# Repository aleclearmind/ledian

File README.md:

# ledian

Welcome to ledian, a color-coded terminal made out of LEDs.

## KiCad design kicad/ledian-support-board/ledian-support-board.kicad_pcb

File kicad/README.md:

# ledian: KiCad projects

This directory contains KiCad projects for PCBs that Ledian uses.
Projects were created with KiCad 7 with no dependencies from external libraries.

## ledian-2.0-small

Prototype of Ledian 2.0, small panel with just 40 LEDs used to create a proof of concept.

## ledian-support-board

Support board for the microcontroller ESP32-C6. The boards mounts the developing board for ESP32-C6 made by Waveshare.
The board has also
 - 3 ADCs to read all the analog signals from temperature/current sensors of PCBs and power supplies
 - a digital temperature/humidity/pressure sensor
 - power good input signals from power supplies
 - voltage level shifter 3.3V -> 5V for LEDs data signals

## ledian-2.0

Full version of Ledian, panels composed by 480 LEDs arranged in a 12 rows and 40 columns that can be tiled to create a standard 80x24 terminal.
Some changes were made to the configuration of signal input and 4 NTC were added to measure PCB's board temperature.

## ledian-LED-PCB-placer

KiCad's plugin that does the majority of the PCB routing for Ledian board with all the LEDs. The plugin procedurally created the
PCB, places all the componentes, routes all the traces and creates filled zones for ground and power supply.
The configurability is limited and very specific to Ledian but it already allows to change number of LEDs, spacing, position/width of traces and other parameters.

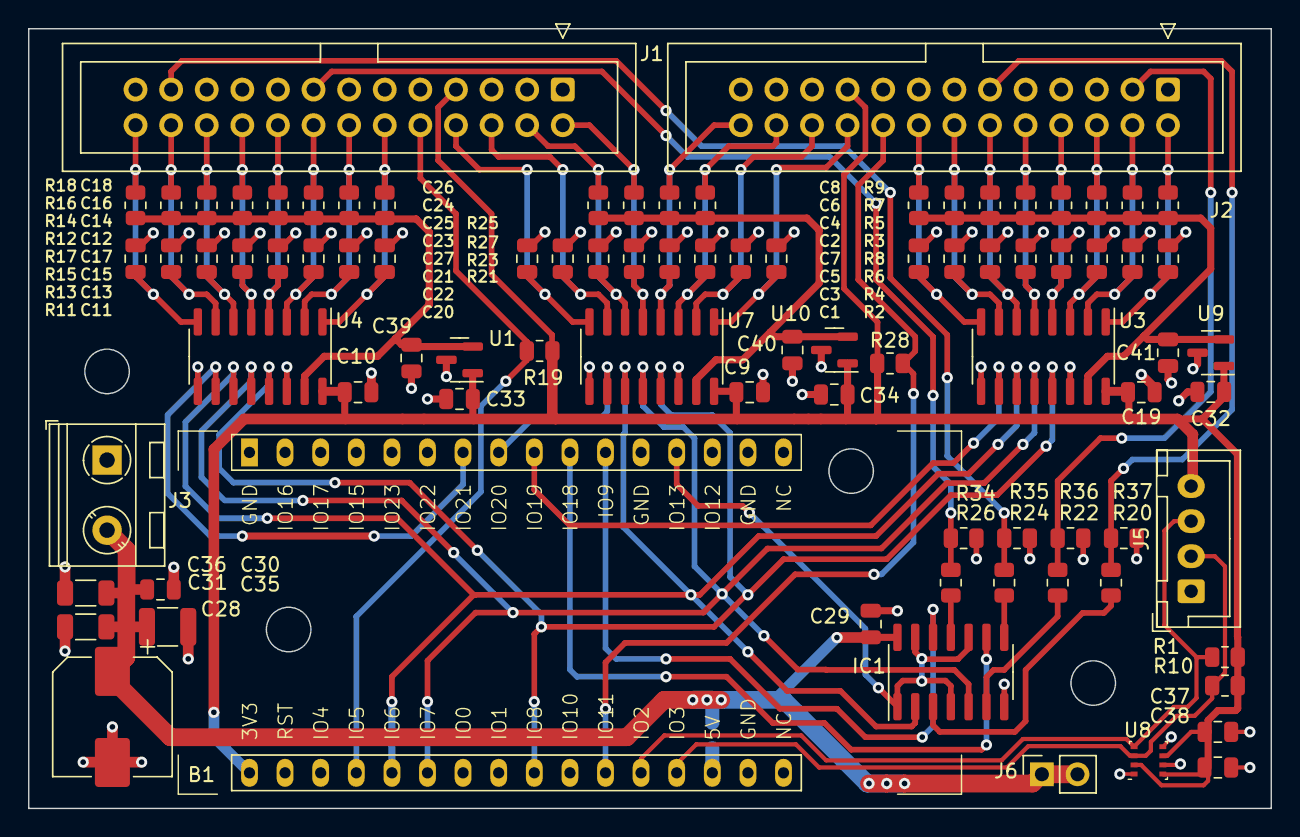
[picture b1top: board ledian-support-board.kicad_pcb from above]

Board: 2 copper layers, 88.6 x 55.6 mm, 88 parts (1 on the bottom side), 50 nets.

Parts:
B1: ESP32-C6_WaveShare
C1, C2, C3, C4, C5, C6, C7, C8, C11, C12, C13, C14, C15, C16, C17, C18, C21, C23, C25, C27: 2.2uF; C_0805_2012Metric
C9, C10, C19, C20, C22, C24, C26, C29, C30, C37, C38: 100nF; C_0805_2012Metric
C28: 100uF; CP_Elec_8x10
C31: 4.7uF; C_1206_3216Metric
C32, C33, C34: 0.47uF; C_0805_2012Metric
C35: 10uF; C_1210_3225Metric
C36: 1uF; C_1206_3216Metric
C39, C40, C41: 1uF; C_0805_2012Metric
IC1: SN74HCT125N; SOIC-14_3.9x8.7mm_P1.27mm
J1, J2: Conn_02x13_Odd_Even; IDC-Header_2x13_P2.54mm_Vertical
J3: TerminalBlock_RND_205-00045_1x02_P5.00mm_Horizontal
J5: Conn_01x04_Pin; JST_XH_B4B-XH-A_1x04_P2.50mm_Vertical
J6: Conn_01x02; PinSocket_1x02_P2.54mm_Vertical
R1, R10: 3.3k; R_0805_2012Metric
R2, R3, R4, R5, R6, R7, R8, R9, R11, R12, R13, R14, R15, R16, R17, R18, R21, R25: 1.6k; R_0805_2012Metric
R19, R28: 22k; R_0805_2012Metric
R20, R22, R24, R26: 300; R_0805_2012Metric
R23, R27: 750; R_0805_2012Metric
R29: 0; R_0805_2012Metric
R34, R35, R36, R37: 4.7k; R_0805_2012Metric
U1, U9, U10: REF3030; SOT-23
U3, U4, U7: MCP3208; SOIC-16_3.9x9.9mm_P1.27mm
U8: BME280; Bosch_LGA-8_2.5x2.5mm_P0.65mm_ClockwisePinNumbering

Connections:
+3V0: C39.1, C40.1, C41.1, R2.1, R3.1, R4.1, R5.1, R6.1, R7.1, R8.1, R9.1, R11.1, R12.1, R13.1, R14.1, R15.1, R16.1, R17.1, R18.1, R21.1, R23.1, R25.1, R27.1, U1.2 (OUT), U3.15 (Vref), U4.15 (Vref), U7.15 (Vref), U9.2 (OUT), U10.2 (OUT)
+3V3: B1.32 (3V3), C9.1, C10.1, C19.1, C32.1, C33.1, C34.1, C37.1, C38.1, J1.7, J2.19, J5.4, R1.1, R10.1, R19.1, R28.1, U1.1 (IN), U3.16 (Vdd), U4.16 (Vdd), U7.16 (Vdd), U8.2 (CSB), U8.6 (VDDIO), U8.8 (VDD), U9.1 (IN), U10.1 (IN)
+5V: C28.1, C29.1, C30.1, C31.1, C35.1, C36.1, IC1.14 (VCC), J3.2, J6.1, J6.2, R29.1
CUR_PANEL_0: C20.1, J2.20, U7.1 (CH0)
CUR_PANEL_1: C22.1, J2.22, U7.2 (CH1)
CUR_PANEL_2: C24.1, J1.6, U7.7 (CH6)
CUR_PANEL_3: C26.1, J1.8, U7.8 (CH7)
GND: B1.1 (GND), B1.12 (GND), B1.15 (GND), B1.18 (GND), C1.2, C2.2, C3.2, C4.2, C5.2, C6.2, C7.2, C8.2, C9.2, C10.2, C11.2, C12.2, C13.2, C14.2, C15.2, C16.2, C17.2, C18.2, C19.2, C20.2, C21.2, C22.2, C23.2, C24.2, C25.2, C26.2, C27.2, C28.2, C29.2, C30.2, C31.2, C32.2, C33.2, C34.2, C35.2, C36.2, C37.2, C38.2, C39.2, C40.2, C41.2, IC1.7 (GND), J1.1, J1.3, J1.5, J1.9, J1.11, J1.13, J1.17, J1.19, J1.21, J1.25, J2.1, J2.5, J2.7, J2.9, J2.13, J2.15, J2.17, J2.21, J2.23, J2.25, J3.1, J5.1, R34.1, R35.1, R36.1, R37.1, U1.3 (GND), U3.9 (DGND), U3.14 (AGND), U4.9 (DGND), U4.14 (AGND), U7.9 (DGND), U7.14 (AGND), U8.1 (GND), U8.5 (SDO), U8.7 (GND), U9.3 (GND), U10.3 (GND)
I2C_SCK: B1.21 (IO2), J5.3, R1.2, U8.4 (SCK)
I2C_SDA: B1.20 (IO3), J5.2, R10.2, U8.3 (SDI)
NTC_0_PANEL_0: C1.1, J2.2, R2.2, U3.1 (CH0)
NTC_0_PANEL_1: C2.1, J2.10, R3.2, U3.5 (CH4)
NTC_0_PANEL_2: C11.1, J1.12, R11.2, U4.1 (CH0)
NTC_0_PANEL_3: C12.1, J1.20, R12.2, U4.5 (CH4)
NTC_1_PANEL_0: C3.1, J2.4, R4.2, U3.2 (CH1)
NTC_1_PANEL_1: C4.1, J2.12, R5.2, U3.6 (CH5)
NTC_1_PANEL_2: C13.1, J1.14, R13.2, U4.2 (CH1)
NTC_1_PANEL_3: C14.1, J1.22, R14.2, U4.6 (CH5)
NTC_2_PANEL_0: C5.1, J2.6, R6.2, U3.3 (CH2)
NTC_2_PANEL_1: C6.1, J2.14, R7.2, U3.7 (CH6)
NTC_2_PANEL_2: C15.1, J1.16, R15.2, U4.3 (CH2)
NTC_2_PANEL_3: C16.1, J1.24, R16.2, U4.7 (CH6)
NTC_3_PANEL_0: C7.1, J2.8, R8.2, U3.4 (CH3)
NTC_3_PANEL_1: C8.1, J2.16, R9.2, U3.8 (CH7)
NTC_3_PANEL_2: C17.1, J1.18, R17.2, U4.4 (CH3)
NTC_3_PANEL_3: C18.1, J1.26, R18.2, U4.8 (CH7)
NTC_PSU_0: C21.1, J2.24, R21.2, U7.3 (CH2)
NTC_PSU_1: C25.1, J1.4, R25.2, U7.6 (CH5)
unnamed: B1.19 (5V), R29.2
unnamed: IC1.3 (1Y), R20.1
unnamed: IC1.6 (2Y), R22.1
unnamed: IC1.8 (3Y), R24.1
unnamed: IC1.11 (4Y), R26.1
PHOTORESIST_0: C23.1, J2.26, R23.2, U7.4 (CH3)
PHOTORESIST_1: C27.1, J1.2, R27.2, U7.5 (CH4)
PSU_GOOD_0: B1.22 (IO11), J2.18, R28.2
PSU_GOOD_1: B1.29 (IO5), J1.10, R19.2
SPI_CLK: B1.24 (IO8), U3.13 (CLK), U4.13 (CLK), U7.13 (CLK)
SPI_CS_ADC_0: B1.9 (IO19), U3.10 (~CS/SHDN)
SPI_CS_ADC_1: B1.7 (IO21), U4.10 (~CS/SHDN)
SPI_CS_ADC_2: B1.8 (IO20), U7.10 (~CS/SHDN)
SPI_CS_LED: B1.13 (IO13), IC1.1 (1~OE), IC1.4 (2~OE), IC1.10 (3~OE), IC1.13 (4~OE)
SPI_IO_0: B1.28 (IO6), IC1.2 (1A), U3.11 (Din), U4.11 (Din), U7.11 (Din)
SPI_IO_1: B1.27 (IO7), IC1.5 (2A), U3.12 (Dout), U4.12 (Dout), U7.12 (Dout)
SPI_IO_2: B1.10 (IO18), IC1.9 (3A)
SPI_IO_3: B1.11 (IO9), IC1.12 (4A)
SPI_PANEL_0: J2.3, R22.2, R36.2
SPI_PANEL_1: J2.11, R20.2, R37.2
SPI_PANEL_2: J1.15, R26.2, R34.2
SPI_PANEL_3: J1.23, R24.2, R35.2

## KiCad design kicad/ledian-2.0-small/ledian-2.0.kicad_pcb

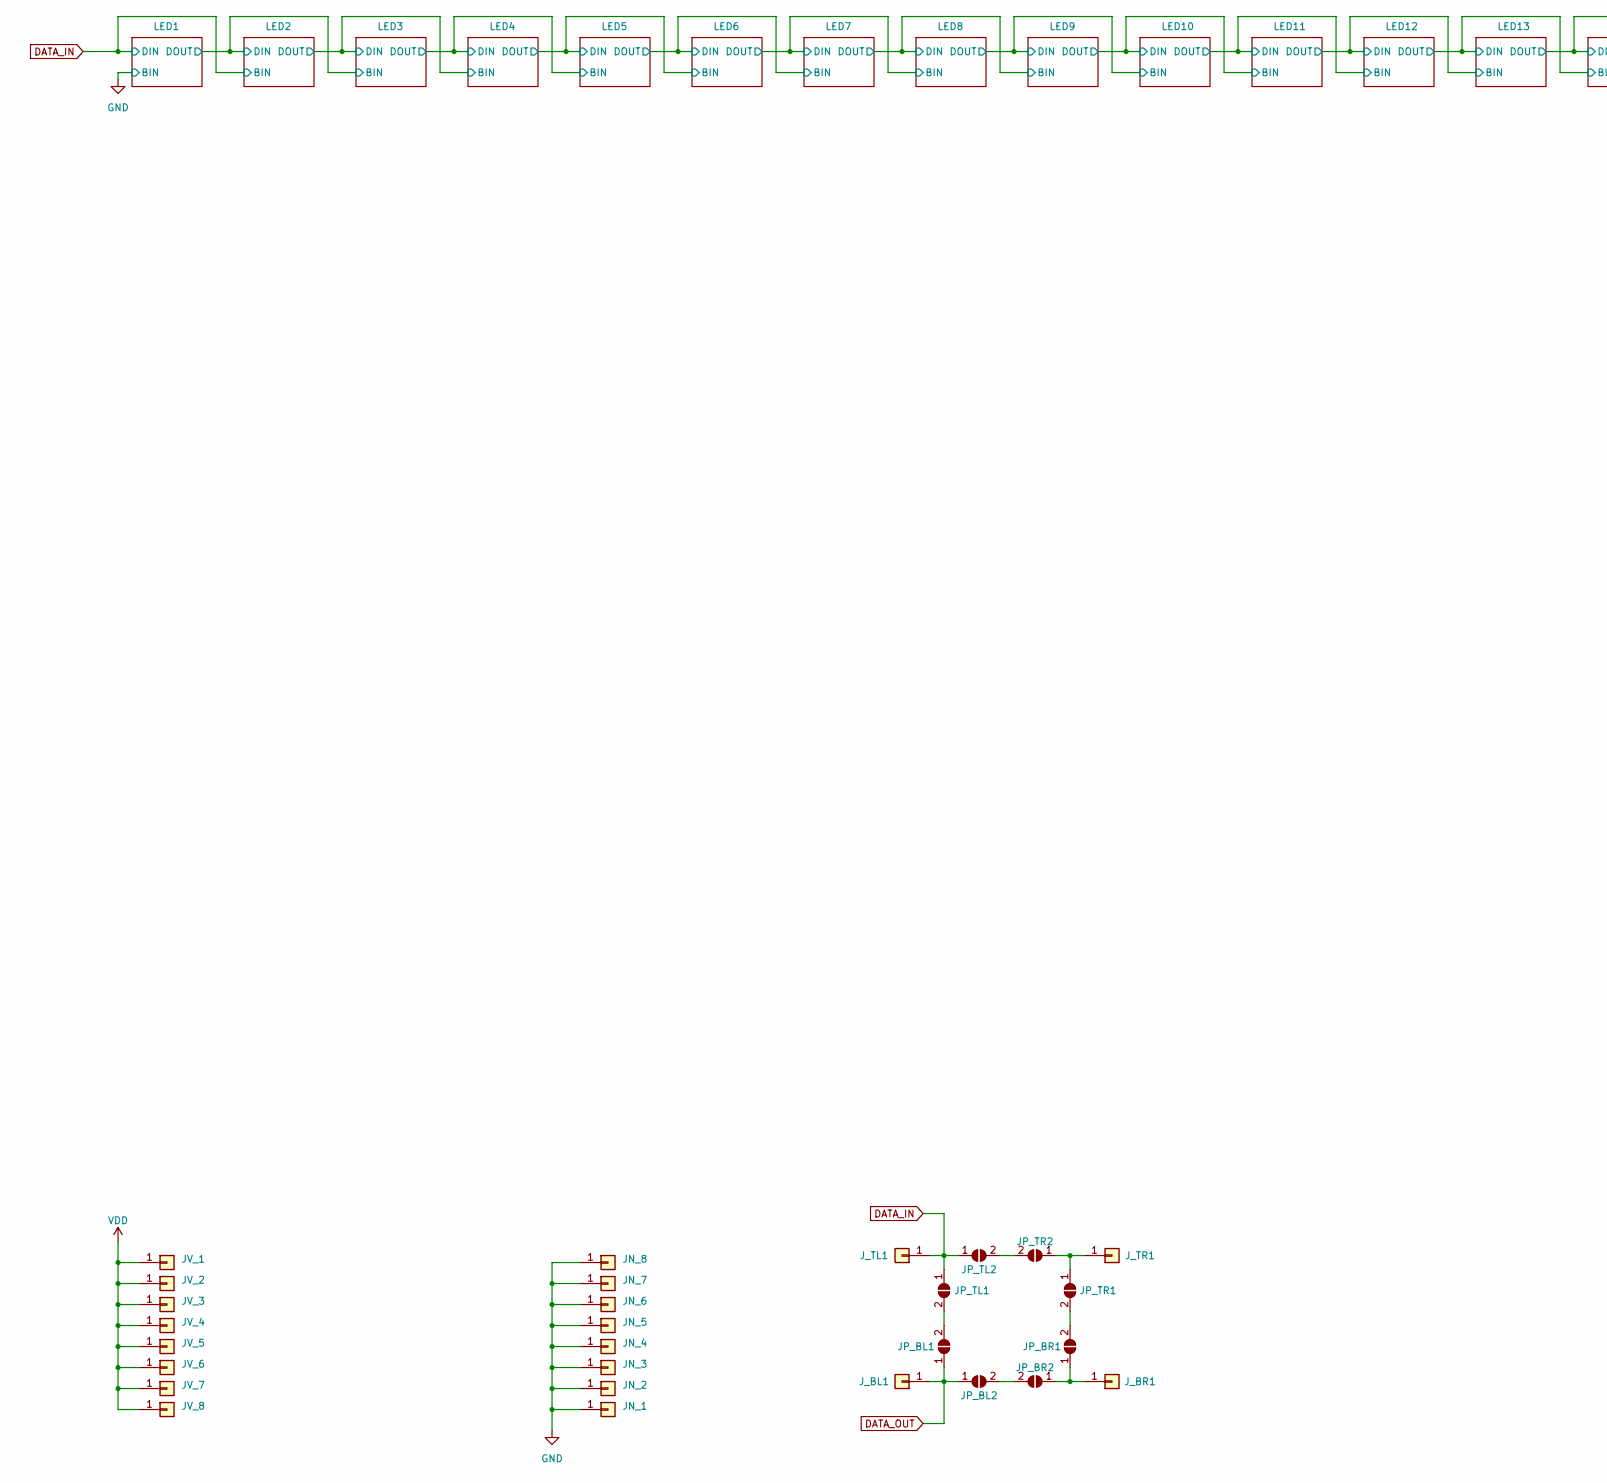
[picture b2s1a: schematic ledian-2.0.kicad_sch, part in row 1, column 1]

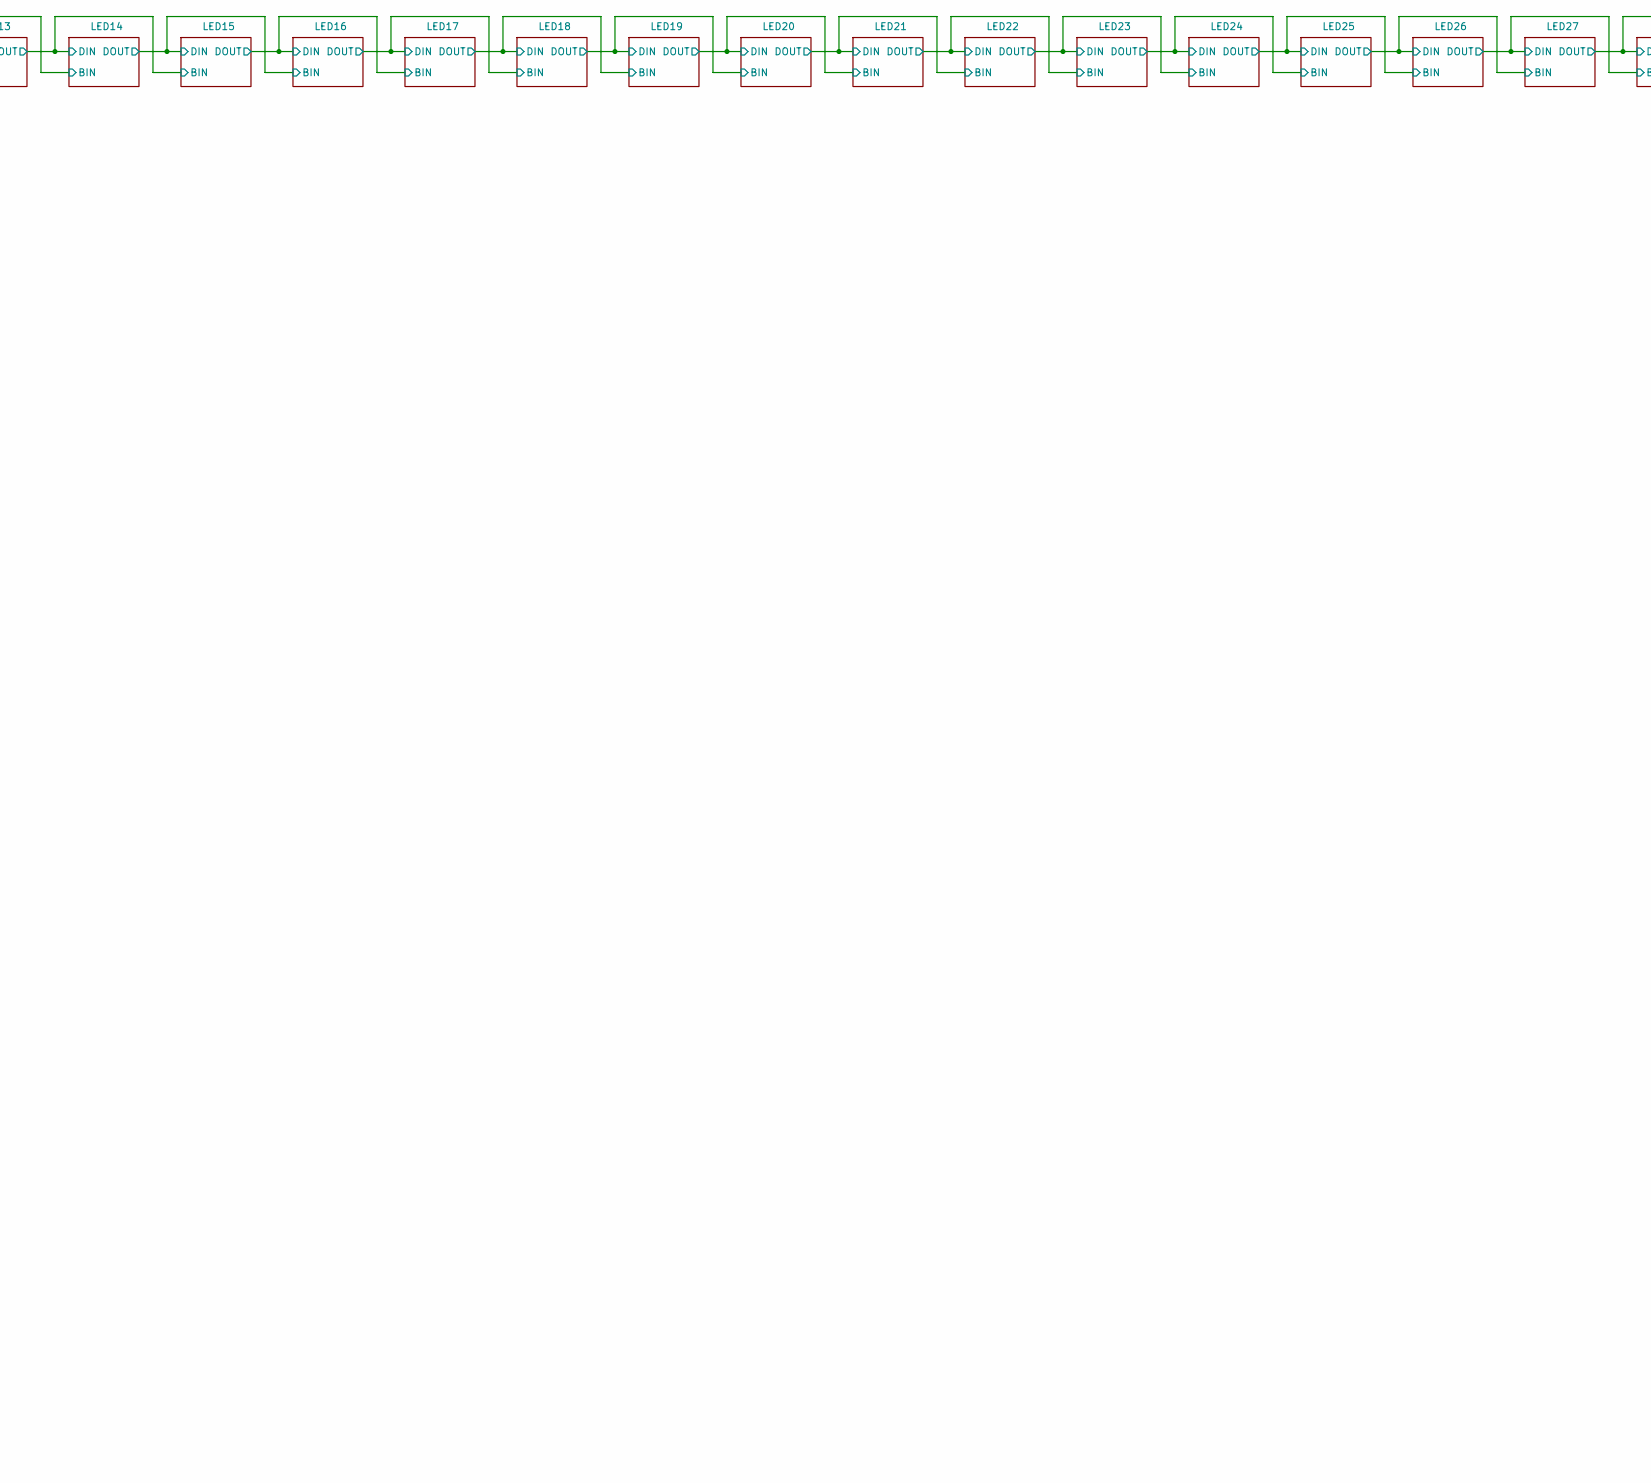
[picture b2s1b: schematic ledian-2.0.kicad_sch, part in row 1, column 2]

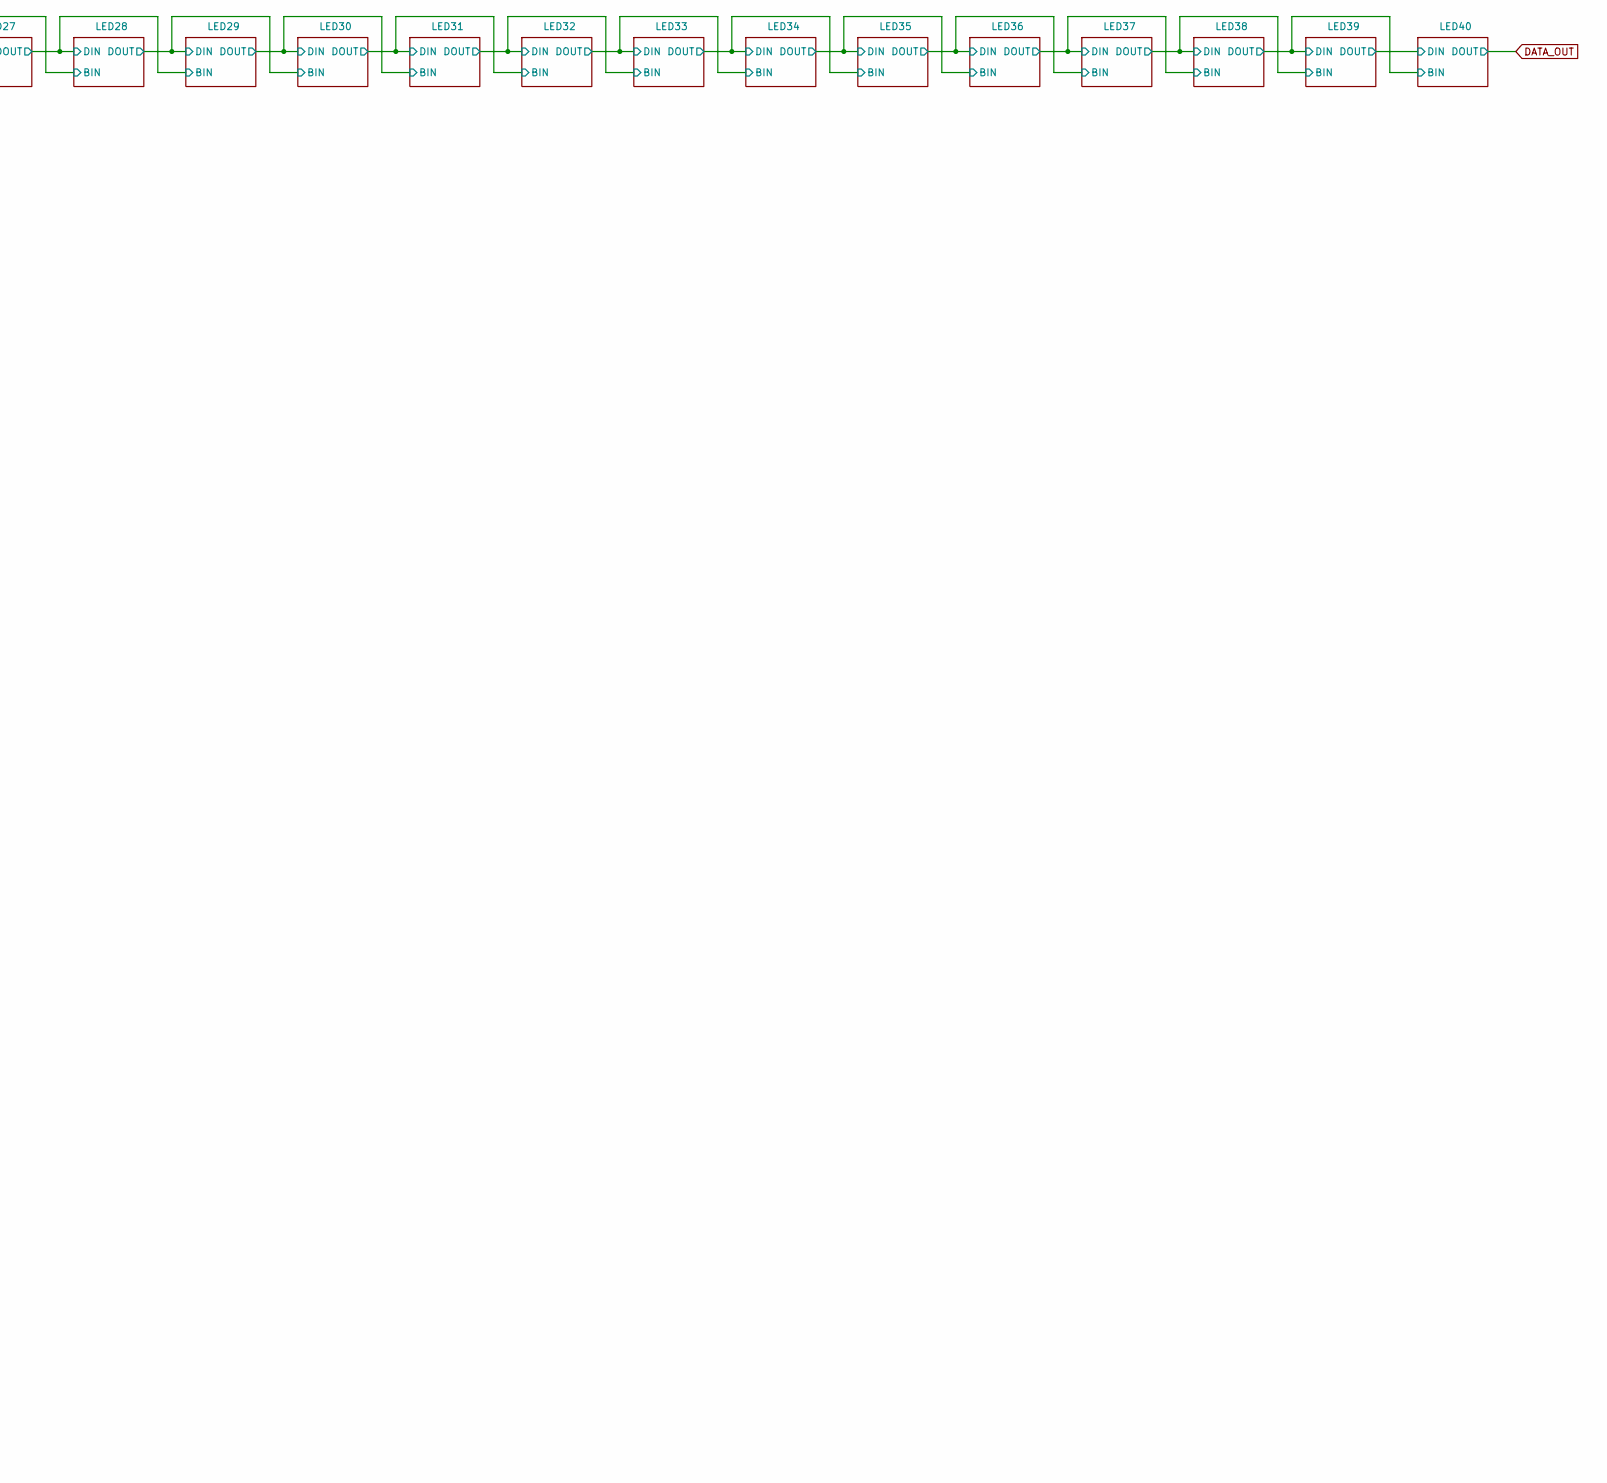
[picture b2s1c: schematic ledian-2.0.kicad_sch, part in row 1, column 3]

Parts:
JN_1, JN_2, JN_3, JN_4, JN_5, JN_6, JN_7, JN_8: Conn_01x01; TestPoint_Pad_4.0x4.0mm
JP_BL1, JP_BL2: SolderJumper_2_Open; SolderJumper-2_P1.3mm_Open_TrianglePad1.0x1.5mm
JP_BR1, JP_BR2: SolderJumper_2_Open; SolderJumper-2_P1.3mm_Open_TrianglePad1.0x1.5mm
JP_TL1, JP_TL2: SolderJumper_2_Open; SolderJumper-2_P1.3mm_Open_TrianglePad1.0x1.5mm
JP_TR1, JP_TR2: SolderJumper_2_Open; SolderJumper-2_P1.3mm_Open_TrianglePad1.0x1.5mm
JV_1, JV_2, JV_3, JV_4, JV_5, JV_6, JV_7, JV_8: Conn_01x01; TestPoint_Pad_4.0x4.0mm
J_BL1: Conn_01x01; TestPoint_Pad_2.5x2.5mm
J_BR1: Conn_01x01; TestPoint_Pad_2.5x2.5mm
J_TL1: Conn_01x01; TestPoint_Pad_2.5x2.5mm
J_TR1: Conn_01x01; TestPoint_Pad_2.5x2.5mm

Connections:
DATA_IN: JP_TL1.1 (A), JP_TL2.1 (A), J_TL1.1; also elsewhere on the board
DATA_OUT: JP_BL1.1 (A), JP_BL2.1 (A), J_BL1.1; also elsewhere on the board
GND: JN_1.1, JN_2.1, JN_3.1, JN_4.1, JN_5.1, JN_6.1, JN_7.1, JN_8.1; also elsewhere on the board
unnamed: JP_BL1.2 (B), JP_TL1.2 (B)
unnamed: JP_BL2.2 (B), JP_BR2.2 (B)
unnamed: JP_BR1.1 (A), JP_BR2.1 (A), J_BR1.1
unnamed: JP_BR1.2 (B), JP_TR1.2 (B)
unnamed: JP_TL2.2 (B), JP_TR2.2 (B)
unnamed: JP_TR1.1 (A), JP_TR2.1 (A), J_TR1.1
VDD: JV_1.1, JV_2.1, JV_3.1, JV_4.1, JV_5.1, JV_6.1, JV_7.1, JV_8.1; also elsewhere on the board

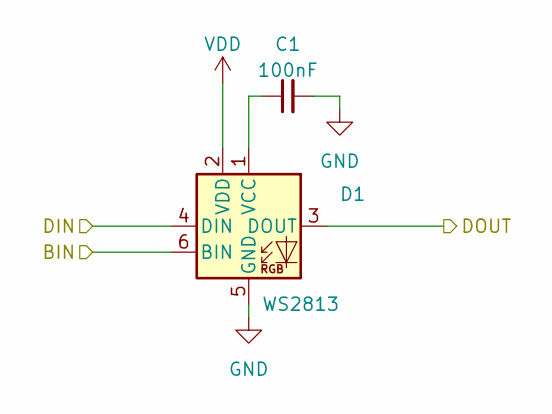
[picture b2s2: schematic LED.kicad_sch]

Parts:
C1: 100nF; C_0805_2012Metric; LCSC C599848
D1: WS2813; LED_WS2812_PLCC6_5.0x5.0mm_P1.6mm; LCSC C5446699

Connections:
/LED1/DOUT: D1.3 (DOUT); also elsewhere on the board
DATA_IN: D1.4 (DIN); also elsewhere on the board
GND: C1.2, D1.5 (GND), D1.6 (BIN); also elsewhere on the board
unnamed: C1.1, D1.1 (VCC)
VDD: D1.2 (VDD); also elsewhere on the board

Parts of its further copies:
C2, C3, C4, C5, C6, C7, C8, C9, C10, C11, C12, C13, C14, C15, C16, C17, C18, C19, C20, C21, C22, C23, C24, C25, C26, C27, C28, C29, C30, C31, C32, C33, C34, C35, C36, C37, C38, C39, C40: 100nF; C_0805_2012Metric; LCSC C599848
D2, D3, D4, D5, D6, D7, D8, D9, D10, D11, D12, D13, D14, D15, D16, D17, D18, D19, D20, D21, D22, D23, D24, D25, D26, D27, D28, D29, D30, D31, D32, D33, D34, D35, D36, D37, D38, D39, D40: WS2813; LED_WS2812_PLCC6_5.0x5.0mm_P1.6mm; LCSC C5446699

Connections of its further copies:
/LED1/DOUT: D2.4 (DIN), D3.6 (BIN); also elsewhere on the board
/LED2/DOUT: D2.3 (DOUT), D3.4 (DIN), D4.6 (BIN)
/LED3/DOUT: D3.3 (DOUT), D4.4 (DIN), D5.6 (BIN)
/LED4/DOUT: D4.3 (DOUT), D5.4 (DIN), D6.6 (BIN)
/LED5/DOUT: D5.3 (DOUT), D6.4 (DIN), D7.6 (BIN)
/LED6/DOUT: D6.3 (DOUT), D7.4 (DIN), D8.6 (BIN)
/LED7/DOUT: D7.3 (DOUT), D8.4 (DIN), D9.6 (BIN)
/LED10/BIN: D8.3 (DOUT), D9.4 (DIN), D10.6 (BIN)
/LED10/DIN: D9.3 (DOUT), D10.4 (DIN), D11.6 (BIN)
/LED10/DOUT: D10.3 (DOUT), D11.4 (DIN), D12.6 (BIN)
/LED11/DOUT: D11.3 (DOUT), D12.4 (DIN), D13.6 (BIN)
/LED12/DOUT: D12.3 (DOUT), D13.4 (DIN), D14.6 (BIN)
/LED13/DOUT: D13.3 (DOUT), D14.4 (DIN), D15.6 (BIN)
/LED14/DOUT: D14.3 (DOUT), D15.4 (DIN), D16.6 (BIN)
/LED15/DOUT: D15.3 (DOUT), D16.4 (DIN), D17.6 (BIN)
/LED16/DOUT: D16.3 (DOUT), D17.4 (DIN), D18.6 (BIN)
/LED17/DOUT: D17.3 (DOUT), D18.4 (DIN), D19.6 (BIN)
/LED18/DOUT: D18.3 (DOUT), D19.4 (DIN), D20.6 (BIN)
/LED19/DOUT: D19.3 (DOUT), D20.4 (DIN), D21.6 (BIN)
/LED20/DOUT: D20.3 (DOUT), D21.4 (DIN), D22.6 (BIN)
/LED21/DOUT: D21.3 (DOUT), D22.4 (DIN), D23.6 (BIN)
/LED22/DOUT: D22.3 (DOUT), D23.4 (DIN), D24.6 (BIN)
/LED23/DOUT: D23.3 (DOUT), D24.4 (DIN), D25.6 (BIN)
/LED24/DOUT: D24.3 (DOUT), D25.4 (DIN), D26.6 (BIN)
/LED25/DOUT: D25.3 (DOUT), D26.4 (DIN), D27.6 (BIN)
/LED26/DOUT: D26.3 (DOUT), D27.4 (DIN), D28.6 (BIN)
/LED27/DOUT: D27.3 (DOUT), D28.4 (DIN), D29.6 (BIN)
/LED28/DOUT: D28.3 (DOUT), D29.4 (DIN), D30.6 (BIN)
/LED29/DOUT: D29.3 (DOUT), D30.4 (DIN), D31.6 (BIN)
/LED30/DOUT: D30.3 (DOUT), D31.4 (DIN), D32.6 (BIN)
/LED31/DOUT: D31.3 (DOUT), D32.4 (DIN), D33.6 (BIN)
/LED32/DOUT: D32.3 (DOUT), D33.4 (DIN), D34.6 (BIN)
/LED33/DOUT: D33.3 (DOUT), D34.4 (DIN), D35.6 (BIN)
/LED34/DOUT: D34.3 (DOUT), D35.4 (DIN), D36.6 (BIN)
/LED35/DOUT: D35.3 (DOUT), D36.4 (DIN), D37.6 (BIN)
/LED36/DOUT: D36.3 (DOUT), D37.4 (DIN), D38.6 (BIN)
/LED37/DOUT: D37.3 (DOUT), D38.4 (DIN), D39.6 (BIN)
/LED38/DOUT: D38.3 (DOUT), D39.4 (DIN), D40.6 (BIN)
/LED39/DOUT: D39.3 (DOUT), D40.4 (DIN)
DATA_IN: D2.6 (BIN); also elsewhere on the board
DATA_OUT: D40.3 (DOUT); also elsewhere on the board
GND: C2.2, C3.2, C4.2, C5.2, C6.2, C7.2, C8.2, C9.2, C10.2, C11.2, C12.2, C13.2, C14.2, C15.2, C16.2, C17.2, C18.2, C19.2, C20.2, C21.2, C22.2, C23.2, C24.2, C25.2, C26.2, C27.2, C28.2, C29.2, C30.2, C31.2, C32.2, C33.2, C34.2, C35.2, C36.2, C37.2, C38.2, C39.2, C40.2, D2.5 (GND), D3.5 (GND), D4.5 (GND), D5.5 (GND), D6.5 (GND), D7.5 (GND), D8.5 (GND), D9.5 (GND), D10.5 (GND), D11.5 (GND), D12.5 (GND), D13.5 (GND), D14.5 (GND), D15.5 (GND), D16.5 (GND), D17.5 (GND), D18.5 (GND), D19.5 (GND), D20.5 (GND), D21.5 (GND), D22.5 (GND), D23.5 (GND), D24.5 (GND), D25.5 (GND), D26.5 (GND), D27.5 (GND), D28.5 (GND), D29.5 (GND), D30.5 (GND), D31.5 (GND), D32.5 (GND), D33.5 (GND), D34.5 (GND), D35.5 (GND), D36.5 (GND), D37.5 (GND), D38.5 (GND), D39.5 (GND), D40.5 (GND); also elsewhere on the board
unnamed: C2.1, D2.1 (VCC)
unnamed: C3.1, D3.1 (VCC)
unnamed: C4.1, D4.1 (VCC)
unnamed: C5.1, D5.1 (VCC)
unnamed: C6.1, D6.1 (VCC)
unnamed: C7.1, D7.1 (VCC)
unnamed: C8.1, D8.1 (VCC)
unnamed: C9.1, D9.1 (VCC)
unnamed: C10.1, D10.1 (VCC)
unnamed: C11.1, D11.1 (VCC)
unnamed: C12.1, D12.1 (VCC)
unnamed: C13.1, D13.1 (VCC)
unnamed: C14.1, D14.1 (VCC)
unnamed: C15.1, D15.1 (VCC)
unnamed: C16.1, D16.1 (VCC)
unnamed: C17.1, D17.1 (VCC)
unnamed: C18.1, D18.1 (VCC)
unnamed: C19.1, D19.1 (VCC)
unnamed: C20.1, D20.1 (VCC)
unnamed: C21.1, D21.1 (VCC)
unnamed: C22.1, D22.1 (VCC)
unnamed: C23.1, D23.1 (VCC)
unnamed: C24.1, D24.1 (VCC)
unnamed: C25.1, D25.1 (VCC)
unnamed: C26.1, D26.1 (VCC)
unnamed: C27.1, D27.1 (VCC)
unnamed: C28.1, D28.1 (VCC)
unnamed: C29.1, D29.1 (VCC)
unnamed: C30.1, D30.1 (VCC)
unnamed: C31.1, D31.1 (VCC)
unnamed: C32.1, D32.1 (VCC)
unnamed: C33.1, D33.1 (VCC)
unnamed: C34.1, D34.1 (VCC)
unnamed: C35.1, D35.1 (VCC)
unnamed: C36.1, D36.1 (VCC)
unnamed: C37.1, D37.1 (VCC)
unnamed: C38.1, D38.1 (VCC)
unnamed: C39.1, D39.1 (VCC)
unnamed: C40.1, D40.1 (VCC)
VDD: D2.2 (VDD), D3.2 (VDD), D4.2 (VDD), D5.2 (VDD), D6.2 (VDD), D7.2 (VDD), D8.2 (VDD), D9.2 (VDD), D10.2 (VDD), D11.2 (VDD), D12.2 (VDD), D13.2 (VDD), D14.2 (VDD), D15.2 (VDD), D16.2 (VDD), D17.2 (VDD), D18.2 (VDD), D19.2 (VDD), D20.2 (VDD), D21.2 (VDD), D22.2 (VDD), D23.2 (VDD), D24.2 (VDD), D25.2 (VDD), D26.2 (VDD), D27.2 (VDD), D28.2 (VDD), D29.2 (VDD), D30.2 (VDD), D31.2 (VDD), D32.2 (VDD), D33.2 (VDD), D34.2 (VDD), D35.2 (VDD), D36.2 (VDD), D37.2 (VDD), D38.2 (VDD), D39.2 (VDD), D40.2 (VDD); also elsewhere on the board

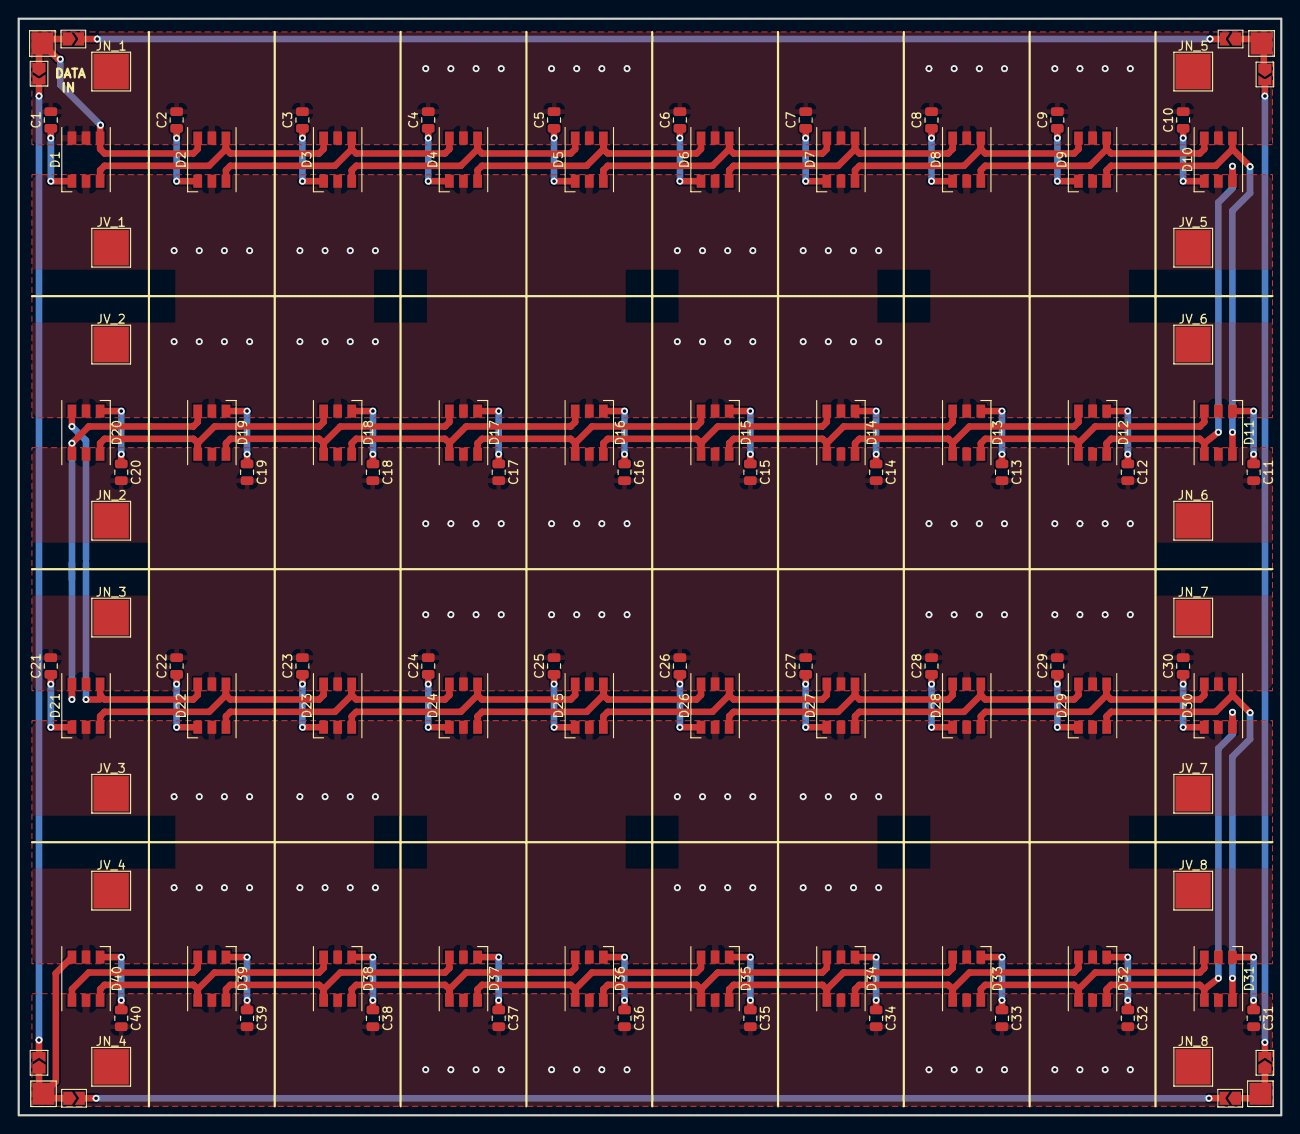
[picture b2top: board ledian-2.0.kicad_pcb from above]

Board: 2 copper layers, 143.4 x 124.5 mm, 108 parts (0 on the bottom side), 89 nets.

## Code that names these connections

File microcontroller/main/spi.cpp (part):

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 * GPIOs definition for SPI using GPIO matrix, more flexibility
 * rather than IOMux and no need to high speeds
 */
#define GPIO_SPI_CLK                    (gpio_num_t) 8
#define GPIO_SPI_LED_CS                 (gpio_num_t) 13
#define GPIO_SPI_ADC1_CS                (gpio_num_t) 19
#define GPIO_SPI_ADC2_CS                (gpio_num_t) 20
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/*
 * GPIOs for reading PSU good signals
 */
#define GPIO_PSU_GOOD_0                 (gpio_num_t) 5
#define GPIO_PSU_GOOD_1                 (gpio_num_t) 11

/*
 * GPIOs for I2C communication with BME280 and other possible
 * external sensors or devices
 */
#define GPIO_I2C_SDA                    (gpio_num_t) 3
#define GPIO_I2C_SCL                    (gpio_num_t) 2

/*
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    const spi_bus_config_t spi_bus_cfg = {
        .data0_io_num = GPIO_SPI_IO0_MOSI,
        .data1_io_num = GPIO_SPI_IO1_MISO,
        .sclk_io_num = GPIO_SPI_CLK,
        .data2_io_num = GPIO_SPI_IO2,
        .data3_io_num = GPIO_SPI_IO3,
        .max_transfer_sz = LEDS_SPI_BUFFER,
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
    const i2c_master_bus_config_t i2c_mst_config = {
        .i2c_port = -1,
        .sda_io_num = GPIO_I2C_SDA,
        .scl_io_num = GPIO_I2C_SCL,
        .clk_source = I2C_CLK_SRC_DEFAULT,
        .glitch_ignore_cnt = 7,
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     * Disable both pullup/pulldown for I2C lines, there's a strong external pullup
     */
    gpio_pullup_en(GPIO_I2C_SCL);
    gpio_pullup_en(GPIO_I2C_SDA);
    gpio_pulldown_dis(GPIO_I2C_SCL);
    gpio_pulldown_dis(GPIO_I2C_SDA);

    /*
     * Set PSU power good signals as input with no pullup/pulldown
     */
    gpio_set_direction(GPIO_PSU_GOOD_0, GPIO_MODE_INPUT);
    gpio_set_direction(GPIO_PSU_GOOD_1, GPIO_MODE_INPUT);
    gpio_pullup_dis(GPIO_PSU_GOOD_0);
    gpio_pullup_dis(GPIO_PSU_GOOD_0);
    gpio_pullup_dis(GPIO_PSU_GOOD_1);
    gpio_pullup_dis(GPIO_PSU_GOOD_1);

    gpio_set_direction(GPIO_STATIC_VS_ANIMATED, GPIO_MODE_INPUT);
    gpio_pullup_en(GPIO_STATIC_VS_ANIMATED);
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
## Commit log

2024-11-19 Initial import
2024-11-26 Added folder for KiCad projects
2024-11-26 Added ledian-support-board KiCad project
2024-11-26 Added ledian-2.0 KiCad project
2024-11-26 Added ledian-2.0-small KiCad project
2024-12-27 Addew new folder with some diagrams
2024-12-27 kicad: ledian-support-board: added titles to all pages
2024-12-27 kicad: ledian-support-board: added some comments to parts of the circuit
2024-12-27 drawings: added new diagram about USB wiring
2024-12-27 kicad: added plugin used to route the PCB of Ledian
2025-01-10 Add missing file
2025-03-14 Added test code for driving WS2812 LEDs directly from Linux
2025-03-14 Added code for microcontroller with acquisition of all sensors
